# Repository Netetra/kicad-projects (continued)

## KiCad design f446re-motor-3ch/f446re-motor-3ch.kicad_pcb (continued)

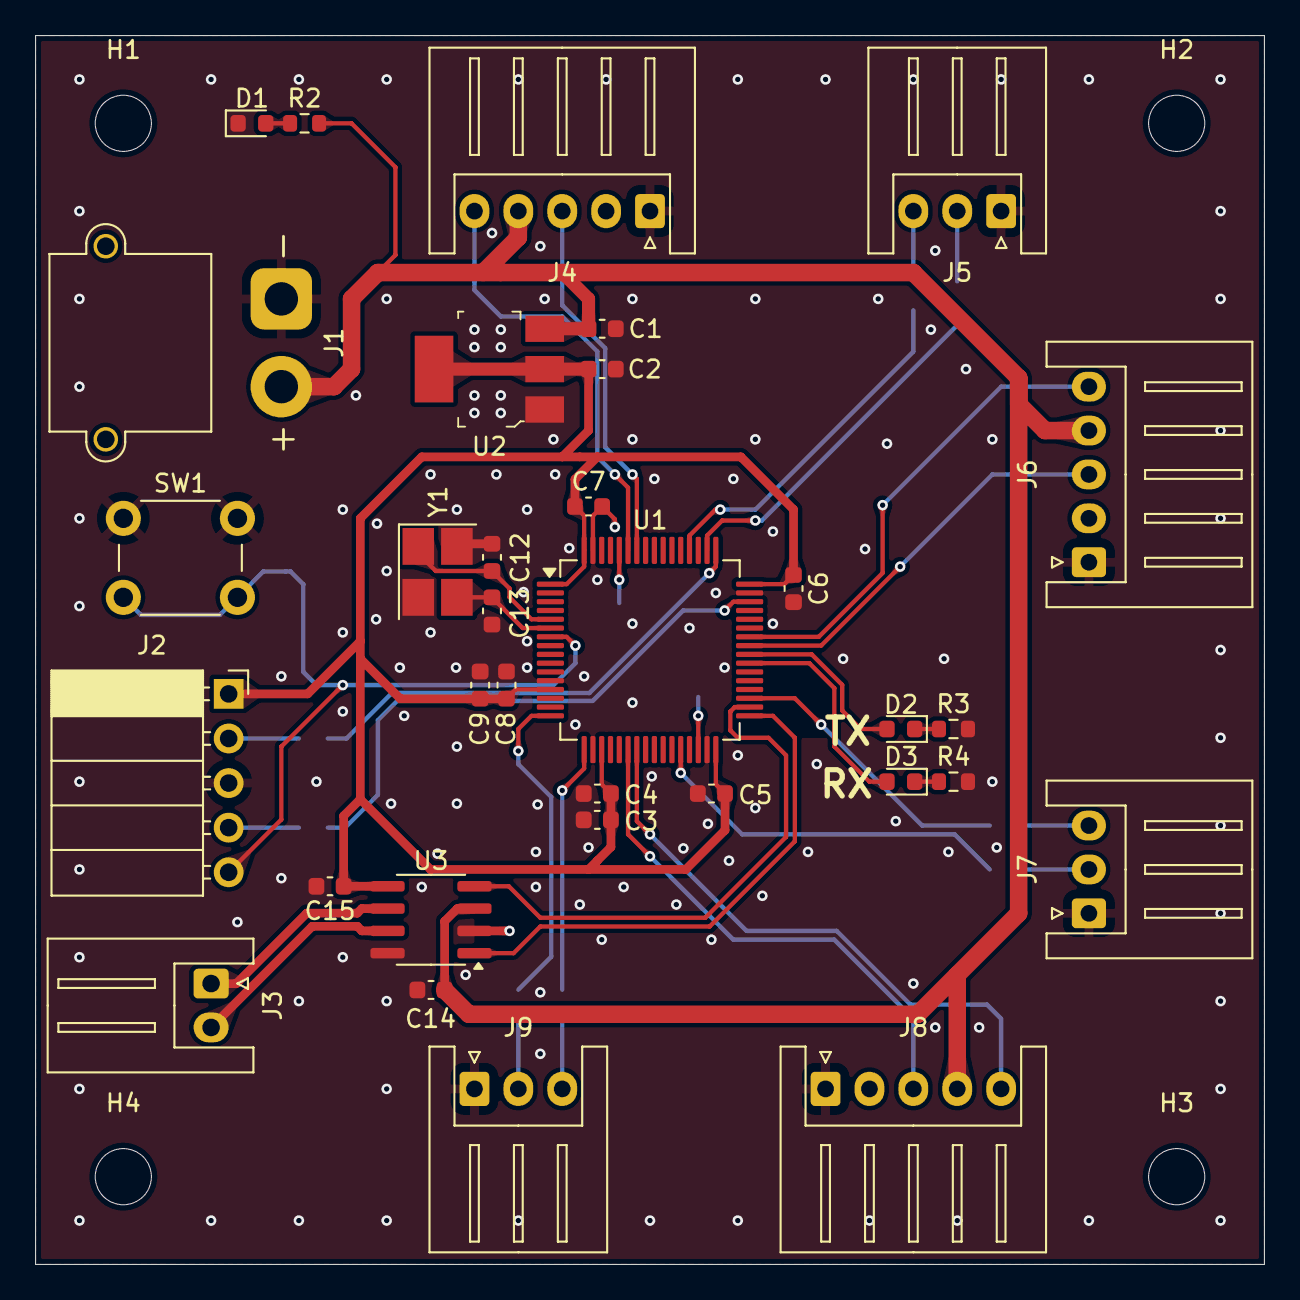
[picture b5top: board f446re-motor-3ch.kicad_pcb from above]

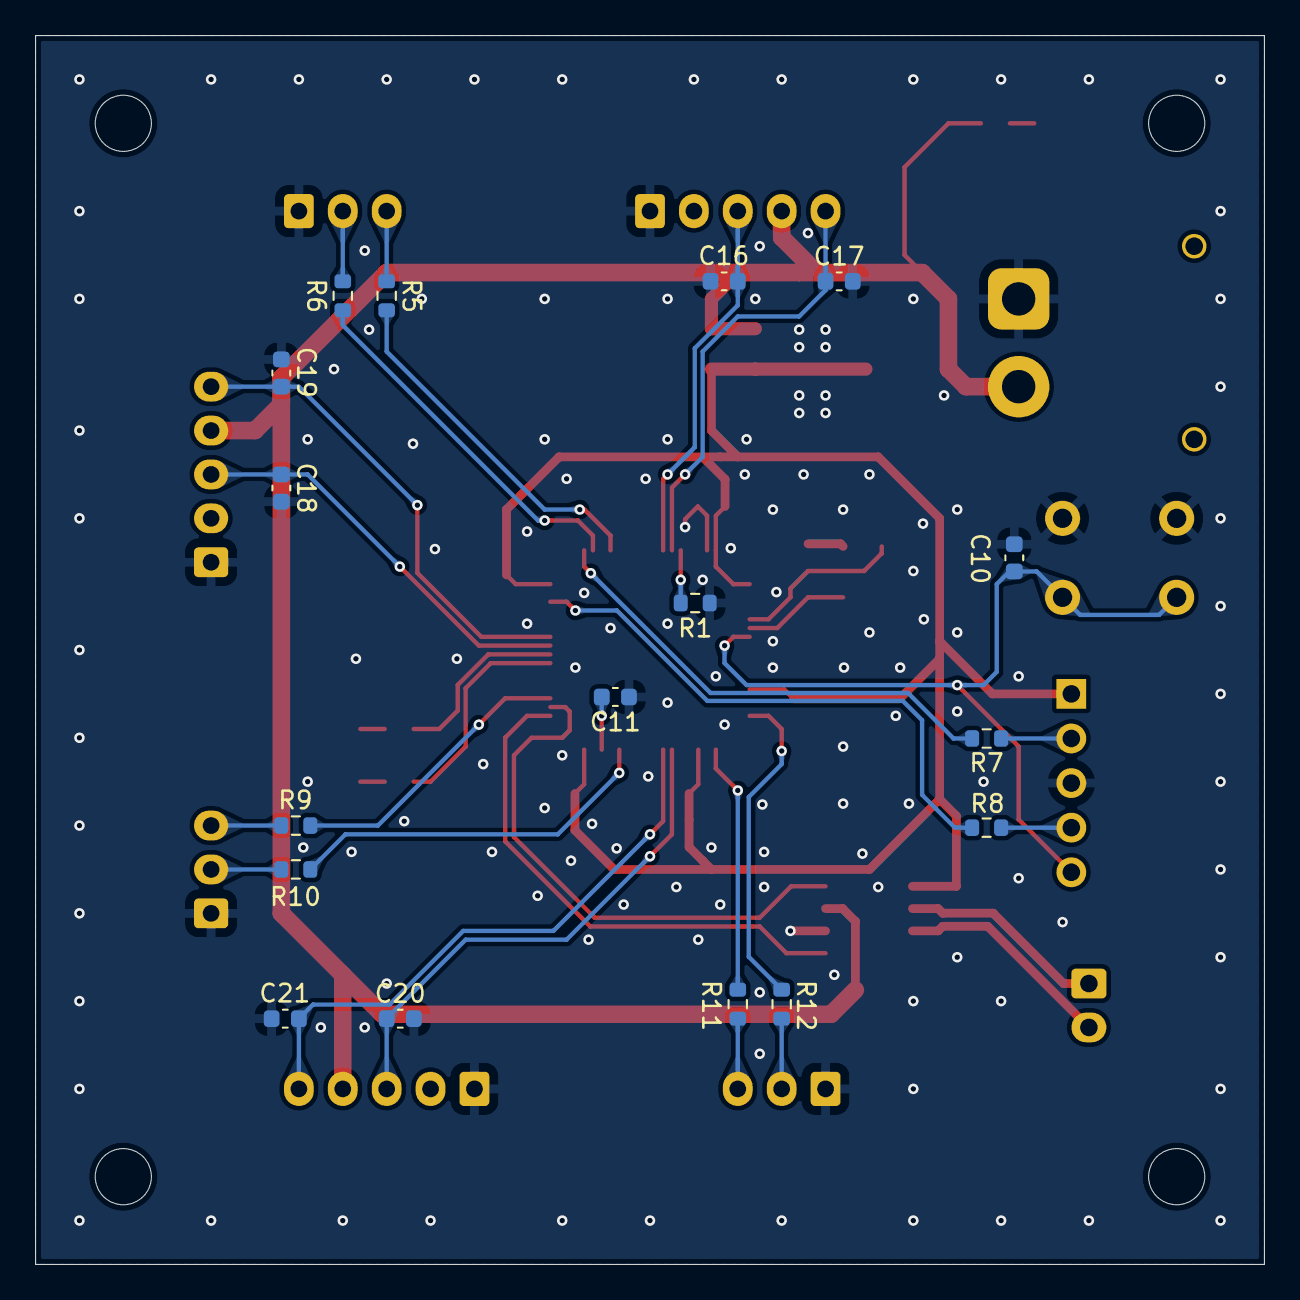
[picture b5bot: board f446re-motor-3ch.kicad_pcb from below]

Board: 2 copper layers, 70.0 x 70.0 mm, 54 parts (17 on the bottom side), 39 nets.

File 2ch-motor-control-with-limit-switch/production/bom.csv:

Designator,Footprint,Quantity,Value,LCSC Part #
C1,0603,1,10uF,
"C10, C14, C15, C4, C5, C6, C7, C8",0603,8,0.1uF,
"C11, C3",0603,2,4.7uF,
"C12, C13",0603,2,15pF,
C2,0603,1,22uF,
C9,0603,1,1uF,
"D1, D2, D3",0603,3,LED,
J1,AMASS_XT30PW-M_1x02_P2.50mm_Horizontal,1,電源コネクタ,
J2,PinSocket_1x05_P2.54mm_Horizontal,1,デバッグ端子,
J3,JST_XH_S2B-XH-A_1x02_P2.50mm_Horizontal,1,CANコネクタ,
"R1, R2, R3, R5, R6",0603,5,1kΩ,
R4,0603,1,10kΩ,
SW1,SW_PUSH_6mm_H5mm,1,リセットスイッチ,
U1,SOT-223-3_TabPin2,1,AZ1117-3.3,
U2,LQFP-64_10x10mm_P0.5mm,1,STM32F446RETx,
U3,SOIC-8_3.9x4.9mm_P1.27mm,1,MCP2562-E-SN,
Y1,Crystal_HC49-4H_Vertical,1,16MHz,

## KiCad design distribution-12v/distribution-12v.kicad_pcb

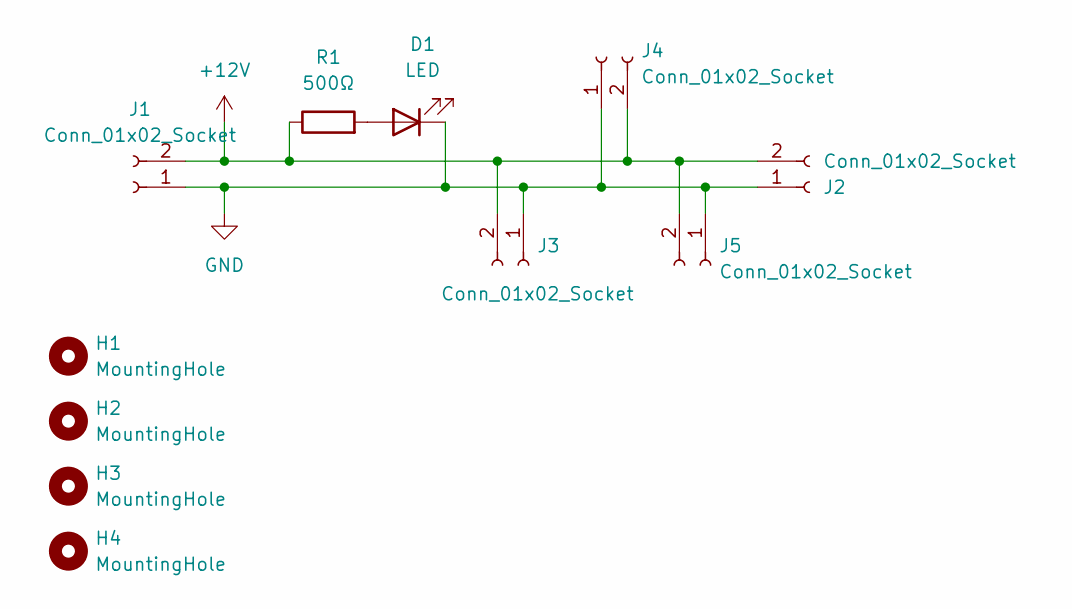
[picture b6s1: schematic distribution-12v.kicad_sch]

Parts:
D1: LED; LED_D5.0mm
H1, H2, H3, H4: MountingHole; MountingHole_3.2mm_M3
J1: Conn_01x02_Socket; AMASS_XT60PW-M_1x02_P7.20mm_Horizontal
J2: Conn_01x02_Socket; AMASS_XT60PW-F_1x02_P7.20mm_Horizontal
J3, J4, J5: Conn_01x02_Socket; AMASS_XT60-F_1x02_P7.20mm_Vertical
R1: 500Ω; R_Axial_DIN0207_L6.3mm_D2.5mm_P7.62mm_Horizontal

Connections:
+12V: J1.2, J2.2, J3.2, J4.2, J5.2, R1.1
GND: D1.1 (K), J1.1, J2.1, J3.1, J4.1, J5.1
unnamed: D1.2 (A), R1.2

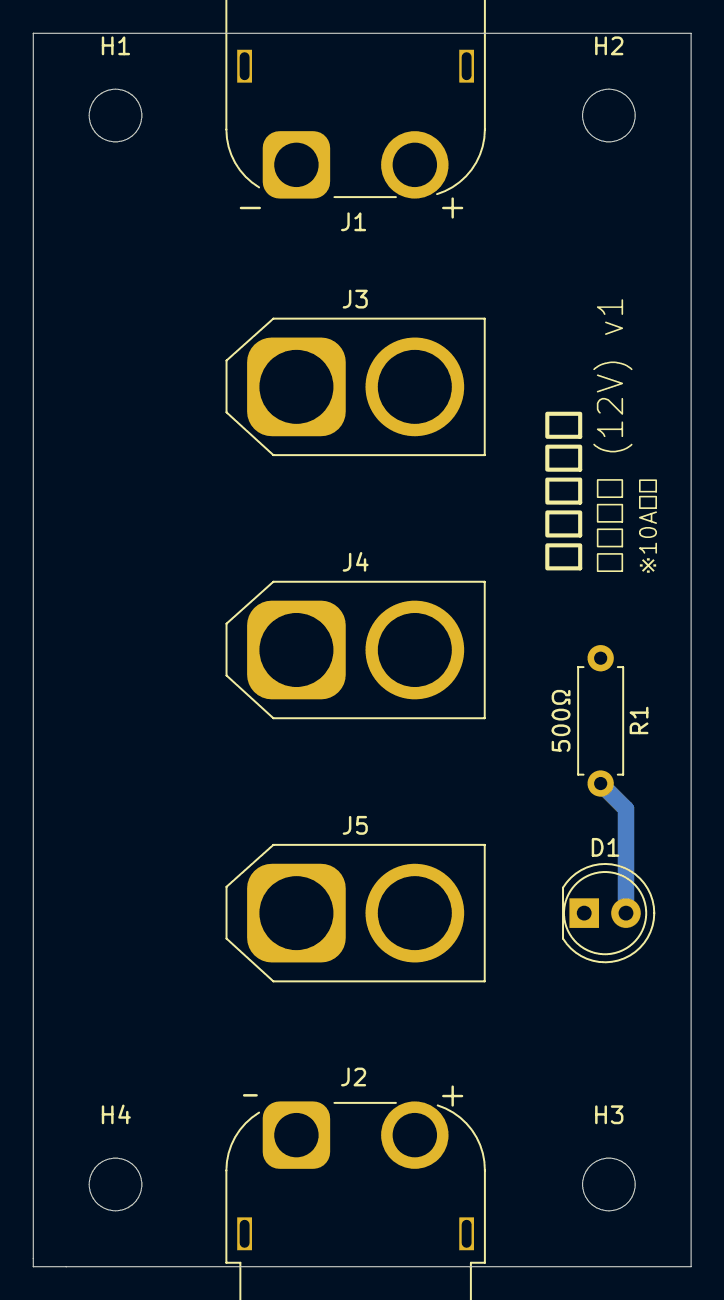
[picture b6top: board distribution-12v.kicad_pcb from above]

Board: 2 copper layers, 40.0 x 75.0 mm, 11 parts (0 on the bottom side), 3 nets.

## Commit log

2024-12-16 feat: 12V用分電基盤
2024-12-17 change: コネクタの数を3つに増やした
2024-12-18 feat: 5V用分電基盤
2024-12-18 feat: 寸法を追加
2024-12-19 fix: まるごと作り直し
2024-12-19 change: 文字を移動
2024-12-19 fix: xt30の固定穴をGNDにした
2024-12-19 change: ???
2024-12-19 change: 文字の向きを揃えた
2025-01-15 feat: QPF64をDIP化する基盤
2025-01-16 change: GNDベタをやめた
2025-01-16 change: 基盤サイズ変更
2025-01-17 change: 配線変更
2025-01-17 change: 配線変更 & 文字追加
2025-01-19 hoge
2025-01-31 2025/01/31/21:22
2025-02-03 2025/02/03/12:25
2025-02-08 2025/02/08/18:16
2025-02-08 2025/02/08/18:17
2025-02-08 2025/02/08/19:35
2025-02-08 2025/02/08/19:51
2025-02-08 2025/02/08/19:56
2025-02-08 2025/02/08/20:30
2025-02-15 2025/02/15/20:27
2025-02-16 2025/02/16/13:41
2025-02-19 2025/02/19/09:55
2025-04-12 feat: PS3コントローラ拡張基盤
2025-04-12 delete: 要らないプロジェクトを削除
2025-04-13 feat: モータ制御基盤にダイオードを追加。オムニ制御基盤を追加
2025-06-09 2025/06/09/23:25
2025-06-09 2025/06/09/23:26
2025-06-26 2025/06/27/01:24
2025-06-30 2025/06/30/17:02
2025-07-08 delete: esp32s3-dip
